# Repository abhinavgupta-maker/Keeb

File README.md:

# Keeb

This is my first ever 75% keyboard which consists of a Rotary encoder, 0.91' Oled Display and 3 Macro keys which helps for shortcuts. 

# Zine

# Usage

I will use this with my laptop almost everyday because i have been using my laptop keyboard ever since and i wanted and upgrade so i made this which fulfills my requirements of both a project and keyboard for everyday. And this would be used a lot by me like i play Games and do coding all day.

# Why did i make this?

I just wanted a personalised keyboard which is not too expensive and has the things i need.

# My motivation to make this

So, i was actually stuck with one project to make for qualification and i am not good at CAD so i wanted a PCB project which can be used by me everyday and i learnt more about PCB designing like all the mistakes i did with routing and layout which made me a lot better in it.

# PCB

# Schematic

# PCB 3D Model

# CAD

# Assembly Steps

1) Get all the things stated in the BOM.
2) Solder all the components as shown in the PCB 3D Model.
3) Get the Case and screws
4) fix the pcb on the stands provides and put the lid
5) use M4 screws and screw the lid down to make sure its fixed
6) Now attach the keycaps on the mechanical switches.
7) now flash your pi pico using the Firmware given
8) Now you are done and you can use the Keyboard Now :)

| Item Name          | Qty | Link                                                                                                                                                                                                                                                                                                                                                                                                                                         | Cost         |
|--------------------|-----|----------------------------------------------------------------------------------------------------------------------------------------------------------------------------------------------------------------------------------------------------------------------------------------------------------------------------------------------------------------------------------------------------------------------------------------------|--------------|
|                    |     |                                                                                                                                                                                                                                                                                                                                                                                                                                              |              |
| Switches           | 90  | https://www.thecosmicbyte.com/product/gateron-mechanical-switches-compatible-with-cosmic-byte-hot-swappable-keyboards-qty-1pc/                                                                                                                                                                                                                                                                                                               | 2.12$/10 pcs |
| Keycaps            | 90  | https://stackskb.com/store/veekos-gradient-keycaps-cherry-profile-135-keys/                                                                                                                                                                                                                                                                                                                                                                  | 13.75$       |
| Rasberry Pi Pico   | 1   | https://quartzcomponents.com/products/raspberry-pi-pico                                                                                                                                                                                                                                                                                                                                                                                      | 3.47$        |
| Rotary Encoder     | 1   | https://robu.in/product/hongyan-ec11h-7ce20p1zy15f7-rotary-encoder-with-push-button-switch-vertical-plug-in-5-pin/?gad_source=1&gad_campaignid=20363337560&gbraid=0AAAAADvLFWdqO2q_Xrig4xmJnp_cJHA4_&gclid=Cj0KCQjwrs7RBhDuARIsAIVfBD0LrHKvlx0CBz3A5sM_YpbGS0aLnzZGAcXy8r_E9EAR5b95Tmu1EuUaAhW_EALw_wcB                                                                                                                                      | 0.58$        |
| Oled Display       | 1   | https://quartzcomponents.com/products/0-91-inch-128x32-blue-oled-display-module-with-i2c-iic-serial-interface?variant=40715109859512&country=IN&currency=INR&utm_medium=product_sync&utm_source=google&utm_content=sag_organic&utm_campaign=sag_organic&gad_source=1&gad_campaignid=21214248935&gbraid=0AAAAACPPFdNRtjhhOKGXBUj8HFQIT7Yin&gclid=Cj0KCQjwrs7RBhDuARIsAIVfBD0tR8qcj7Xi9ig0nD5XjqENH5DQIMJlOxkzwPt6ByNBCNqtdGxbNSYaAr7uEALw_wcB | 1.59$        |
| SK6812 mini E-LEDS | 80  | https://www.lcsc.com/product-detail/C5149201.html?s_z=n_SK6812MINI-E                                                                                                                                                                                                                                                                                                                                                                         | 6.27$        |
| Diodes             | 90  | https://www.lcsc.com/product-detail/C84410.html                                                                                                                                                                                                                                                                                                                                                                                              | 1.65$        |
| PCB                | 5   |                                                                                                                                                                                                                                                                                                                                                                                                                                              | 4$           |
|                    |     |                                                                                                                                                                                                                                                                                                                                                                                                                                              |              |
|                    |     | Total:                                                                                                                                                                                                                                                                                                                                                                                                                                       | 50$ (Approx) |

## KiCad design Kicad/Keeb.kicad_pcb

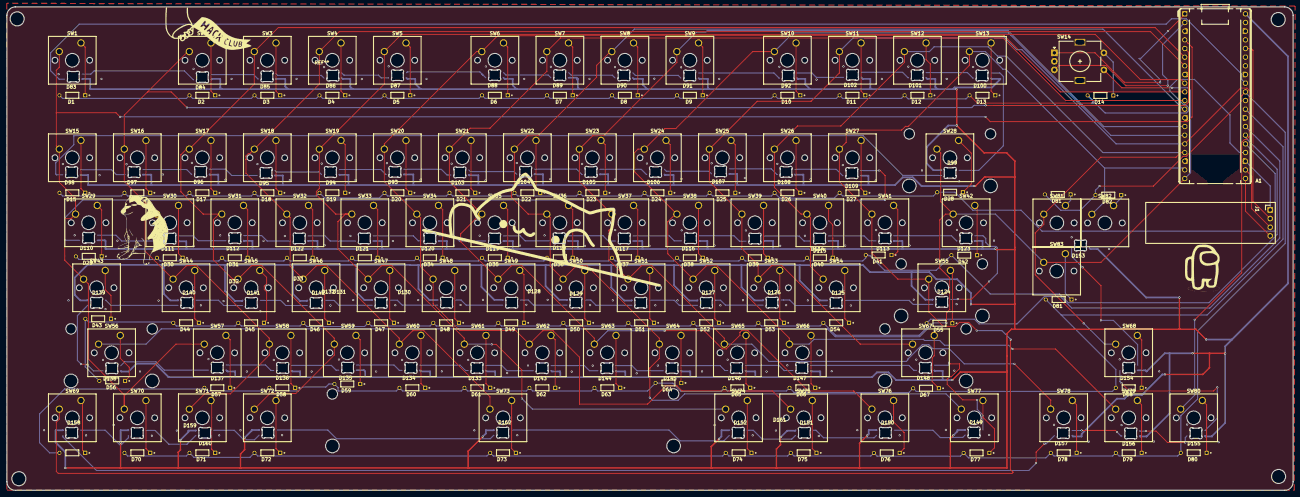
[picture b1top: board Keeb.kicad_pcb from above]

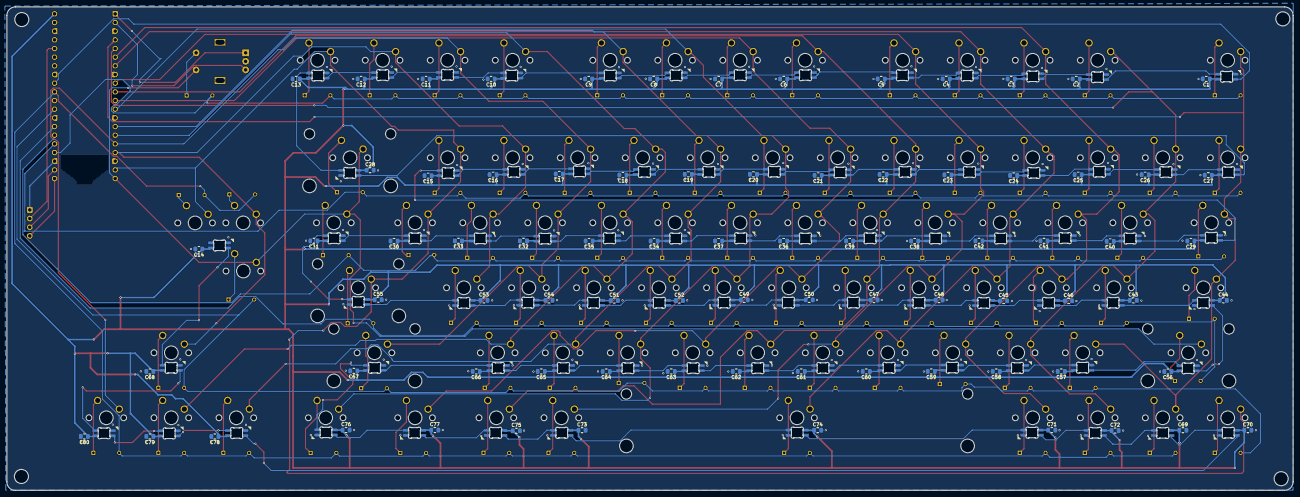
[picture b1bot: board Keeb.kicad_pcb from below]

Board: 2 copper layers, 376.9 x 141.6 mm, 328 parts (80 on the bottom side), 190 nets.

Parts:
A1: RaspberryPi_Pico; RaspberryPi_Pico_Common_THT
C1: 100n; C_0805_2012Metric_Pad1.18x1.45mm_HandSolder
C2, C3, C4, C5, C6, C7, C8, C9, C11, C12, C13, C14, C15, C16, C17, C18, C19, C20, C21, C22, C23, C24, C25, C26, C27, C28, C29, C30, C31, C32, C33, C34, C35, C36, C37, C38, C39, C40, C41, C42, C43, C44, C45, C46, C47, C48, C49, C50, C51, C52, C53, C54, C55, C56, C57, C58, C59, C60, C61, C62, C63, C64, C65, C66, C67, C68, C69, C70, C71, C72, C73, C74, C75, C76, C77, C78, C79, C80: C; C_0805_2012Metric_Pad1.18x1.45mm_HandSolder
C10: 100nF; C_0805_2012Metric_Pad1.18x1.45mm_HandSolder
D1, D2, D3, D4, D5, D6, D7, D8, D9, D10, D11, D12, D13, D14, D15, D16, D17, D18, D19, D20, D21, D22, D23, D24, D25, D26, D27, D28, D29, D30, D31, D32, D33, D34, D35, D36, D37, D38, D39, D40, D41, D42, D43, D44, D45, D46, D47, D48, D49, D50, D51, D52, D53, D54, D55, D56, D57, D58, D59, D60, D61, D62, D63, D64, D65, D66, D67, D68, D69, D70, D71, D72, D73, D74, D75, D76, D77, D78, D79, D80, D81, D81#2, D82: 1N914WT; DIOAD753W49L380D172B
D83, D84, D85, D86, D87, D88, D89, D90, D91, D92, D93, D94, D95, D96, D97, D98, D99, D100, D101, D102, D103, D104, D105, D106, D107, D108, D109, D110, D111, D112, D113, D114, D115, D116, D117, D118, D119, D120, D121, D122, D123, D124, D125, D126, D127, D128, D129, D130, D131, D132, D133, D134, D135, D136, D137, D138, D139, D140, D141, D142, D143, D144, D145, D146, D147, D148, D149, D150, D151, D152, D153, D154, D155, D156, D157, D158, D159, D160, D161, D162: SK6812MINI-E; SK6812MINI-E_fixed
J1: Conn_01x04_Pin; ER_OLEDM0.91_1x-I2C
SW1, SW2, SW3, SW4, SW5, SW6, SW7, SW8, SW9, SW10, SW11, SW12, SW13, SW15, SW16, SW17, SW18, SW19, SW20, SW21, SW22, SW23, SW24, SW25, SW26, SW27, SW30, SW31, SW32, SW33, SW34, SW35, SW36, SW37, SW38, SW39, SW40, SW41, SW44, SW45, SW46, SW47, SW48, SW49, SW50, SW51, SW52, SW53, SW54, SW57, SW58, SW59, SW60, SW61, SW62, SW63, SW64, SW65, SW66, SW68, SW69, SW70, SW71, SW72, SW74, SW75, SW78, SW79, SW80, SW81, SW82, SW83: SW_Push_45deg; SW_Cherry_MX_1.00u_PCB
SW14: RotaryEncoder_Switch; RotaryEncoder_Alps_EC11E-Switch_Vertical_H20mm
SW28: SW_Push_45deg; SW_Cherry_MX_2.00u_PCB
SW29, SW42, SW76: SW_Push_45deg; SW_Cherry_MX_1.50u_PCB
SW43: SW_Push_45deg; SW_Cherry_MX_1.75u_PCB
SW55, SW56: SW_Push_45deg; SW_Cherry_MX_2.25u_PCB
SW67: SW_Push_45deg; SW_Cherry_MX_2.75u_PCB
SW73: SW_Push_45deg; SW_Cherry_MX_6.25u_PCB
SW77: SW_Push_45deg; SW_Cherry_MX_1.25u_PCB

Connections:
+3.3V: A1.36 (3V3), J1.2
+5V: A1.40 (VBUS), C1.1, C2.1, C3.1, C4.1, C5.1, C6.1, C7.1, C8.1, C9.1, C10.1, C11.1, C12.1, C13.1, C14.1, C15.1, C16.1, C17.1, C18.1, C19.1, C20.1, C21.1, C22.1, C23.1, C24.1, C25.1, C26.1, C27.1, C28.1, C29.1, C30.1, C31.1, C32.1, C33.1, C34.1, C35.1, C36.1, C37.1, C38.1, C39.1, C40.1, C41.1, C42.1, C43.1, C44.1, C45.1, C46.1, C47.1, C48.1, C49.1, C50.1, C51.1, C52.1, C53.1, C54.1, C55.1, C56.1, C57.1, C58.1, C59.1, C60.1, C61.1, C62.1, C63.1, C64.1, C65.1, C66.1, C67.1, C68.1, C69.1, C70.1, C71.1, C72.1, C73.1, C74.1, C75.1, C76.1, C77.1, C78.1, C79.1, C80.1, D83.1 (VDD), D84.1 (VDD), D85.1 (VDD), D86.1 (VDD), D87.1 (VDD), D88.1 (VDD), D89.1 (VDD), D90.1 (VDD), D91.1 (VDD), D92.1 (VDD), D93.1 (VDD), D94.1 (VDD), D95.1 (VDD), D96.1 (VDD), D97.1 (VDD), D98.1 (VDD), D99.1 (VDD), D100.1 (VDD), D101.1 (VDD), D102.1 (VDD), D103.1 (VDD), D104.1 (VDD), D105.1 (VDD), D106.1 (VDD), D107.1 (VDD), D108.1 (VDD), D109.1 (VDD), D110.1 (VDD), D111.1 (VDD), D112.1 (VDD), D113.1 (VDD), D114.1 (VDD), D115.1 (VDD), D116.1 (VDD), D117.1 (VDD), D118.1 (VDD), D119.1 (VDD), D120.1 (VDD), D121.1 (VDD), D122.1 (VDD), D123.1 (VDD), D124.1 (VDD), D125.1 (VDD), D126.1 (VDD), D127.1 (VDD), D128.1 (VDD), D129.1 (VDD), D130.1 (VDD), D131.1 (VDD), D132.1 (VDD), D133.1 (VDD), D134.1 (VDD), D135.1 (VDD), D136.1 (VDD), D137.1 (VDD), D138.1 (VDD), D139.1 (VDD), D140.1 (VDD), D141.1 (VDD), D142.1 (VDD), D143.1 (VDD), D144.1 (VDD), D145.1 (VDD), D146.1 (VDD), D147.1 (VDD), D148.1 (VDD), D149.1 (VDD), D150.1 (VDD), D151.1 (VDD), D152.1 (VDD), D153.1 (VDD), D154.1 (VDD), D155.1 (VDD), D156.1 (VDD), D157.1 (VDD), D158.1 (VDD), D159.1 (VDD), D160.1 (VDD), D161.1 (VDD), D162.1 (VDD)
COL1: A1.4 (GPIO2), SW1.2, SW15.2, SW29.2, SW43.2, SW57.2, SW70.2
COL2: A1.5 (GPIO3), SW2.2, SW16.2, SW30.2, SW44.2, SW58.2, SW71.2
COL3: A1.6 (GPIO4), SW3.2, SW17.2, SW31.2, SW45.2, SW59.2, SW72.2
COL4: A1.7 (GPIO5), SW4.2, SW18.2, SW32.2, SW46.2, SW60.2, SW73.2
COL5: A1.9 (GPIO6), SW5.2, SW19.2, SW33.2, SW47.2, SW61.2, SW74.2
COL6: A1.10 (GPIO7), SW6.2, SW20.2, SW34.2, SW48.2, SW62.2, SW75.2
COL7: A1.11 (GPIO8), SW7.2, SW21.2, SW35.2, SW49.2, SW63.2, SW76.2
COL8: A1.12 (GPIO9), SW8.2, SW22.2, SW36.2, SW50.2, SW64.2, SW77.2
COL9: A1.14 (GPIO10), SW9.2, SW23.2, SW37.2, SW51.2, SW65.2, SW78.2
COL10: A1.15 (GPIO11), SW10.2, SW24.2, SW38.2, SW52.2, SW66.2, SW79.2
COL11: A1.16 (GPIO12), SW11.2, SW25.2, SW39.2, SW53.2, SW67.2, SW80.2
COL12: A1.17 (GPIO13), SW12.2, SW26.2, SW40.2, SW54.2, SW68.2, SW81.2
COL13: A1.19 (GPIO14), SW13.2, SW27.2, SW41.2, SW55.2, SW69.2, SW82.2
COL14: A1.20 (GPIO15), SW14.S1, SW28.2, SW42.2, SW56.2, SW83.2
GND: A1.3 (GND), A1.8 (GND), A1.13 (GND), A1.18 (GND), A1.23 (GND), A1.28 (GND), A1.38 (GND), C1.2, C2.2, C3.2, C4.2, C5.2, C6.2, C7.2, C8.2, C9.2, C10.2, C11.2, C12.2, C13.2, C14.2, C15.2, C16.2, C17.2, C18.2, C19.2, C20.2, C21.2, C22.2, C23.2, C24.2, C25.2, C26.2, C27.2, C28.2, C29.2, C30.2, C31.2, C32.2, C33.2, C34.2, C35.2, C36.2, C37.2, C38.2, C39.2, C40.2, C41.2, C42.2, C43.2, C44.2, C45.2, C46.2, C47.2, C48.2, C49.2, C50.2, C51.2, C52.2, C53.2, C54.2, C55.2, C56.2, C57.2, C58.2, C59.2, C60.2, C61.2, C62.2, C63.2, C64.2, C65.2, C66.2, C67.2, C68.2, C69.2, C70.2, C71.2, C72.2, C73.2, C74.2, C75.2, C76.2, C77.2, C78.2, C79.2, C80.2, D83.3 (VSS), D84.3 (VSS), D85.3 (VSS), D86.3 (VSS), D87.3 (VSS), D88.3 (VSS), D89.3 (VSS), D90.3 (VSS), D91.3 (VSS), D92.3 (VSS), D93.3 (VSS), D94.3 (VSS), D95.3 (VSS), D96.3 (VSS), D97.3 (VSS), D98.3 (VSS), D99.3 (VSS), D100.3 (VSS), D101.3 (VSS), D102.3 (VSS), D103.3 (VSS), D104.3 (VSS), D105.3 (VSS), D106.3 (VSS), D107.3 (VSS), D108.3 (VSS), D109.3 (VSS), D110.3 (VSS), D111.3 (VSS), D112.3 (VSS), D113.3 (VSS), D114.3 (VSS), D115.3 (VSS), D116.3 (VSS), D117.3 (VSS), D118.3 (VSS), D119.3 (VSS), D120.3 (VSS), D121.3 (VSS), D122.3 (VSS), D123.3 (VSS), D124.3 (VSS), D125.3 (VSS), D126.3 (VSS), D127.3 (VSS), D128.3 (VSS), D129.3 (VSS), D130.3 (VSS), D131.3 (VSS), D132.3 (VSS), D133.3 (VSS), D134.3 (VSS), D135.3 (VSS), D136.3 (VSS), D137.3 (VSS), D138.3 (VSS), D139.3 (VSS), D140.3 (VSS), D141.3 (VSS), D142.3 (VSS), D143.3 (VSS), D144.3 (VSS), D145.3 (VSS), D146.3 (VSS), D147.3 (VSS), D148.3 (VSS), D149.3 (VSS), D150.3 (VSS), D151.3 (VSS), D152.3 (VSS), D153.3 (VSS), D154.3 (VSS), D155.3 (VSS), D156.3 (VSS), D157.3 (VSS), D158.3 (VSS), D159.3 (VSS), D160.3 (VSS), D161.3 (VSS), D162.3 (VSS), J1.1, SW14.C
unnamed: D1.2 (A), SW1.1
unnamed: D2.2 (A), SW2.1
unnamed: D3.2 (A), SW3.1
unnamed: D4.2 (A), SW4.1
unnamed: D5.2 (A), SW5.1
unnamed: D6.2 (A), SW6.1
unnamed: D7.2 (A), SW7.1
unnamed: D8.2 (A), SW8.1
unnamed: D9.2 (A), SW9.1
unnamed: D10.2 (A), SW10.1
unnamed: D11.2 (A), SW11.1
unnamed: D12.2 (A), SW12.1
unnamed: D13.2 (A), SW13.1
unnamed: D15.2 (A), SW15.1
unnamed: D16.2 (A), SW16.1
unnamed: D17.2 (A), SW17.1
unnamed: D18.2 (A), SW18.1
unnamed: D19.2 (A), SW19.1
unnamed: D20.2 (A), SW20.1
unnamed: D21.2 (A), SW21.1
unnamed: D22.2 (A), SW22.1
unnamed: D23.2 (A), SW23.1
unnamed: D24.2 (A), SW24.1
unnamed: D25.2 (A), SW25.1
unnamed: D26.2 (A), SW26.1
unnamed: D27.2 (A), SW27.1
unnamed: D28.2 (A), SW28.1
unnamed: D29.2 (A), SW29.1
unnamed: D30.2 (A), SW30.1
unnamed: D31.2 (A), SW31.1
unnamed: D32.2 (A), SW32.1
unnamed: D33.2 (A), SW33.1
unnamed: D34.2 (A), SW34.1
unnamed: D35.2 (A), SW35.1
unnamed: D36.2 (A), SW36.1
unnamed: D37.2 (A), SW37.1
unnamed: D38.2 (A), SW38.1
unnamed: D39.2 (A), SW39.1
unnamed: D40.2 (A), SW40.1
unnamed: D41.2 (A), SW41.1
unnamed: D42.2 (A), SW42.1
unnamed: D43.2 (A), SW43.1
unnamed: D44.2 (A), SW44.1
unnamed: D45.2 (A), SW45.1
unnamed: D46.2 (A), SW46.1
unnamed: D47.2 (A), SW47.1
unnamed: D48.2 (A), SW48.1
unnamed: D49.2 (A), SW49.1
unnamed: D50.2 (A), SW50.1
unnamed: D51.2 (A), SW51.1
unnamed: D52.2 (A), SW52.1
unnamed: D53.2 (A), SW53.1
unnamed: D54.2 (A), SW54.1
unnamed: D55.2 (A), SW55.1
unnamed: D56.2 (A), SW56.1
unnamed: D57.2 (A), SW57.1
unnamed: D58.2 (A), SW58.1
unnamed: D59.2 (A), SW59.1
unnamed: D60.2 (A), SW60.1
unnamed: D61.2 (A), SW61.1
unnamed: D62.2 (A), SW62.1
unnamed: D63.2 (A), SW63.1
unnamed: D64.2 (A), SW64.1
unnamed: D65.2 (A), SW65.1
unnamed: D66.2 (A), SW66.1
unnamed: D67.2 (A), SW67.1
unnamed: D68.2 (A), SW68.1
unnamed: D69.2 (A), SW69.1
unnamed: D70.2 (A), SW70.1
unnamed: D71.2 (A), SW71.1
unnamed: D72.2 (A), SW72.1
unnamed: D73.2 (A), SW73.1
unnamed: D74.2 (A), SW74.1
unnamed: D75.2 (A), SW75.1
unnamed: D76.2 (A), SW76.1
unnamed: D77.2 (A), SW77.1
unnamed: D78.2 (A), SW78.1
unnamed: D79.2 (A), SW79.1
unnamed: D80.2 (A), SW80.1
unnamed: D81#2.2 (A), SW81.1
unnamed: D82.2 (A), SW82.1
unnamed: D83.2 (DOUT), D84.4 (DIN)
unnamed: D84.2 (DOUT), D85.4 (DIN)
unnamed: D85.2 (DOUT), D86.4 (DIN)
unnamed: D86.2 (DOUT), D87.4 (DIN)
unnamed: D87.2 (DOUT), D88.4 (DIN)
unnamed: D88.2 (DOUT), D89.4 (DIN)
unnamed: D89.2 (DOUT), D90.4 (DIN)
unnamed: D90.2 (DOUT), D91.4 (DIN)
unnamed: D91.2 (DOUT), D92.4 (DIN)
unnamed: D93.4 (DIN), D94.2 (DOUT)
unnamed: D94.4 (DIN), D95.2 (DOUT)
unnamed: D95.4 (DIN), D96.2 (DOUT)
unnamed: D96.4 (DIN), D97.2 (DOUT)
unnamed: D97.4 (DIN), D98.2 (DOUT)
unnamed: D98.4 (DIN), D99.2 (DOUT)
unnamed: D100.4 (DIN), D101.2 (DOUT)
unnamed: D99.4 (DIN), D100.2 (DOUT)
unnamed: D101.4 (DIN), D102.2 (DOUT)
unnamed: D92.2 (DOUT), D102.4 (DIN)
unnamed: D93.2 (DOUT), D103.4 (DIN)
unnamed: D103.2 (DOUT), D104.4 (DIN)
unnamed: D104.2 (DOUT), D105.4 (DIN)
unnamed: D105.2 (DOUT), D106.4 (DIN)
unnamed: D106.2 (DOUT), D107.4 (DIN)
unnamed: D107.2 (DOUT), D108.4 (DIN)
unnamed: D108.2 (DOUT), D109.4 (DIN)
unnamed: D109.2 (DOUT), D110.4 (DIN)
unnamed: D110.2 (DOUT), D111.4 (DIN)
unnamed: D111.2 (DOUT), D112.4 (DIN)
unnamed: D112.2 (DOUT), D122.4 (DIN)
unnamed: D113.4 (DIN), D114.2 (DOUT)
unnamed: D113.2 (DOUT), D123.4 (DIN)
unnamed: D114.4 (DIN), D115.2 (DOUT)
unnamed: D115.4 (DIN), D116.2 (DOUT)
unnamed: D116.4 (DIN), D117.2 (DOUT)
unnamed: D117.4 (DIN), D118.2 (DOUT)
unnamed: D118.4 (DIN), D119.2 (DOUT)
unnamed: D119.4 (DIN), D120.2 (DOUT)
unnamed: D120.4 (DIN), D121.2 (DOUT)
unnamed: D121.4 (DIN), D122.2 (DOUT)
unnamed: D123.2 (DOUT), D124.4 (DIN)
unnamed: D124.2 (DOUT), D125.4 (DIN)
unnamed: D125.2 (DOUT), D126.4 (DIN)
unnamed: D126.2 (DOUT), D127.4 (DIN)
unnamed: D127.2 (DOUT), D128.4 (DIN)
unnamed: D128.2 (DOUT), D129.4 (DIN)
unnamed: D129.2 (DOUT), D130.4 (DIN)
unnamed: D130.2 (DOUT), D131.4 (DIN)
unnamed: D131.2 (DOUT), D132.4 (DIN)
unnamed: D132.2 (DOUT), D142.4 (DIN)
unnamed: D133.4 (DIN), D134.2 (DOUT)
unnamed: D133.2 (DOUT), D143.4 (DIN)
unnamed: D134.4 (DIN), D135.2 (DOUT)
unnamed: D135.4 (DIN), D136.2 (DOUT)
unnamed: D136.4 (DIN), D137.2 (DOUT)
unnamed: D137.4 (DIN), D138.2 (DOUT)
unnamed: D138.4 (DIN), D139.2 (DOUT)
unnamed: D139.4 (DIN), D140.2 (DOUT)
unnamed: D140.4 (DIN), D141.2 (DOUT)
unnamed: D141.4 (DIN), D142.2 (DOUT)
unnamed: D81.2 (A), SW83.1
unnamed: D143.2 (DOUT), D144.4 (DIN)
unnamed: D144.2 (DOUT), D145.4 (DIN)
unnamed: D145.2 (DOUT), D146.4 (DIN)
unnamed: D146.2 (DOUT), D147.4 (DIN)
unnamed: D147.2 (DOUT), D148.4 (DIN)
unnamed: D148.2 (DOUT), D149.4 (DIN)
unnamed: D149.2 (DOUT), D150.4 (DIN)
unnamed: D150.2 (DOUT), D151.4 (DIN)
unnamed: D151.2 (DOUT), D152.4 (DIN)
unnamed: D152.2 (DOUT), D162.4 (DIN)
unnamed: D153.4 (DIN), D154.2 (DOUT)
unnamed: D154.4 (DIN), D155.2 (DOUT)
unnamed: D155.4 (DIN), D156.2 (DOUT)
unnamed: D156.4 (DIN), D157.2 (DOUT)
unnamed: D157.4 (DIN), D158.2 (DOUT)
unnamed: D158.4 (DIN), D159.2 (DOUT)
unnamed: D159.4 (DIN), D160.2 (DOUT)
unnamed: D160.4 (DIN), D161.2 (DOUT)
unnamed: D161.4 (DIN), D162.2 (DOUT)
RES_A1: A1.1 (GPIO0), SW14.A
RES_B1: A1.2 (GPIO1), SW14.B
RES_M2: D14.2 (A), SW14.S2
RGB: A1.32 (GPIO27_ADC1), D83.4 (DIN)
ROW1: A1.24 (GPIO18), D1.1 (K), D2.1 (K), D3.1 (K), D4.1 (K), D5.1 (K), D6.1 (K), D7.1 (K), D8.1 (K), D9.1 (K), D10.1 (K), D11.1 (K), D12.1 (K), D13.1 (K), D14.1 (K)
ROW2: A1.25 (GPIO19), D15.1 (K), D16.1 (K), D17.1 (K), D18.1 (K), D19.1 (K), D20.1 (K), D21.1 (K), D22.1 (K), D23.1 (K), D24.1 (K), D25.1 (K), D26.1 (K), D27.1 (K), D28.1 (K)
ROW3: A1.26 (GPIO20), D29.1 (K), D30.1 (K), D31.1 (K), D32.1 (K), D33.1 (K), D34.1 (K), D35.1 (K), D36.1 (K), D37.1 (K), D38.1 (K), D39.1 (K), D40.1 (K), D41.1 (K), D42.1 (K)
ROW4: A1.27 (GPIO21), D43.1 (K), D44.1 (K), D45.1 (K), D46.1 (K), D47.1 (K), D48.1 (K), D49.1 (K), D50.1 (K), D51.1 (K), D52.1 (K), D53.1 (K), D54.1 (K), D55.1 (K), D56.1 (K)
ROW5: A1.29 (GPIO22), D57.1 (K), D58.1 (K), D59.1 (K), D60.1 (K), D61.1 (K), D62.1 (K), D63.1 (K), D64.1 (K), D65.1 (K), D66.1 (K), D67.1 (K), D68.1 (K), D69.1 (K), D81.1 (K)
ROW6: A1.31 (GPIO26_ADC0), D70.1 (K), D71.1 (K), D72.1 (K), D73.1 (K), D74.1 (K), D75.1 (K), D76.1 (K), D77.1 (K), D78.1 (K), D79.1 (K), D80.1 (K), D81#2.1 (K), D82.1 (K)
SCL: A1.22 (GPIO17), J1.3
SDA: A1.21 (GPIO16), J1.4

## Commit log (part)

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2026-06-19 Rename Screenshot 2026-06-18 215316.png to Keyboard_3DModel.png
2026-06-19 Rename Screenshot 2026-06-18 221835.png to PCB.png
2026-06-19 Rename Screenshot 2026-06-18 221851.png to Schematic_Switches.png
2026-06-19 Rename Screenshot 2026-06-18 221909.png to RGB_Sch.png
2026-06-19 Rename Screenshot 2026-06-19 095840.png to PCB_3dModel.png
2026-06-19 Rename Screenshot 2026-06-19 100125.png to Open3dModel.png
2026-06-19 Rename KEEB.pdf to Zine.pdf
2026-06-23 Rename Zine (3).pdf to Zine.pdf
2026-06-23 Rename merged (pdf.io).pdf to Zine.pdf
